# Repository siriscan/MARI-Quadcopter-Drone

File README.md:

# MARI-Quadcopter-Drone
A final senior project created by Seth Iris Canonigo, Christopher Ruiz-Guerra, Nahom Solomon, and Connor Prior

*(Omori is a good game btw)*

# 3D PCB

Read 'Report.pdf' for the full project writeup.

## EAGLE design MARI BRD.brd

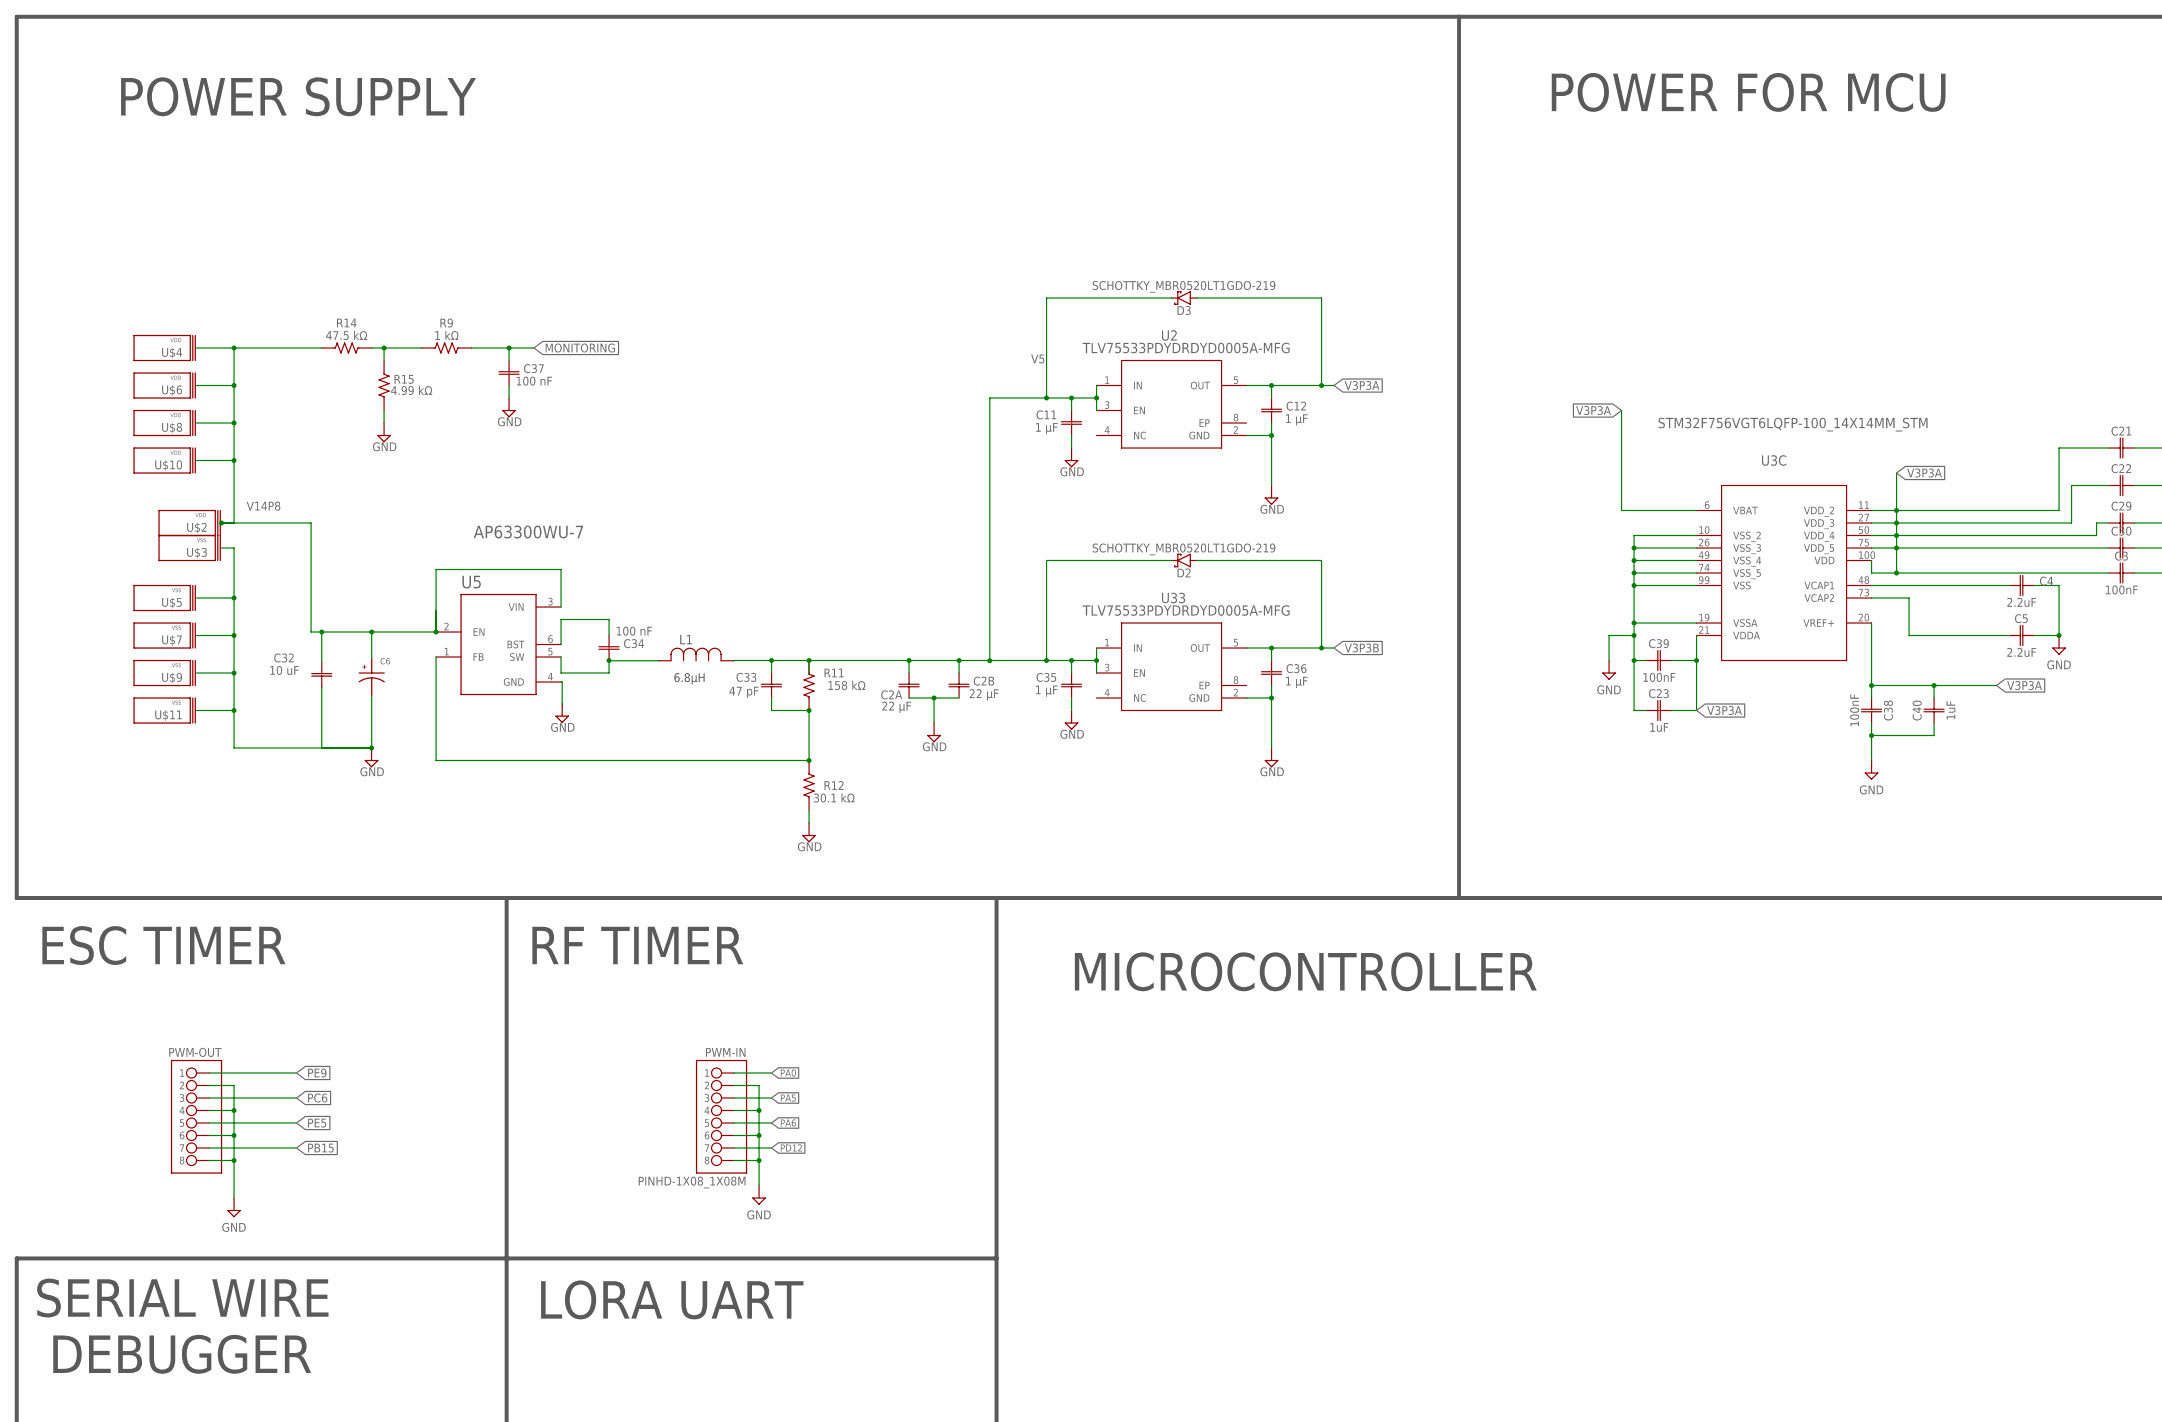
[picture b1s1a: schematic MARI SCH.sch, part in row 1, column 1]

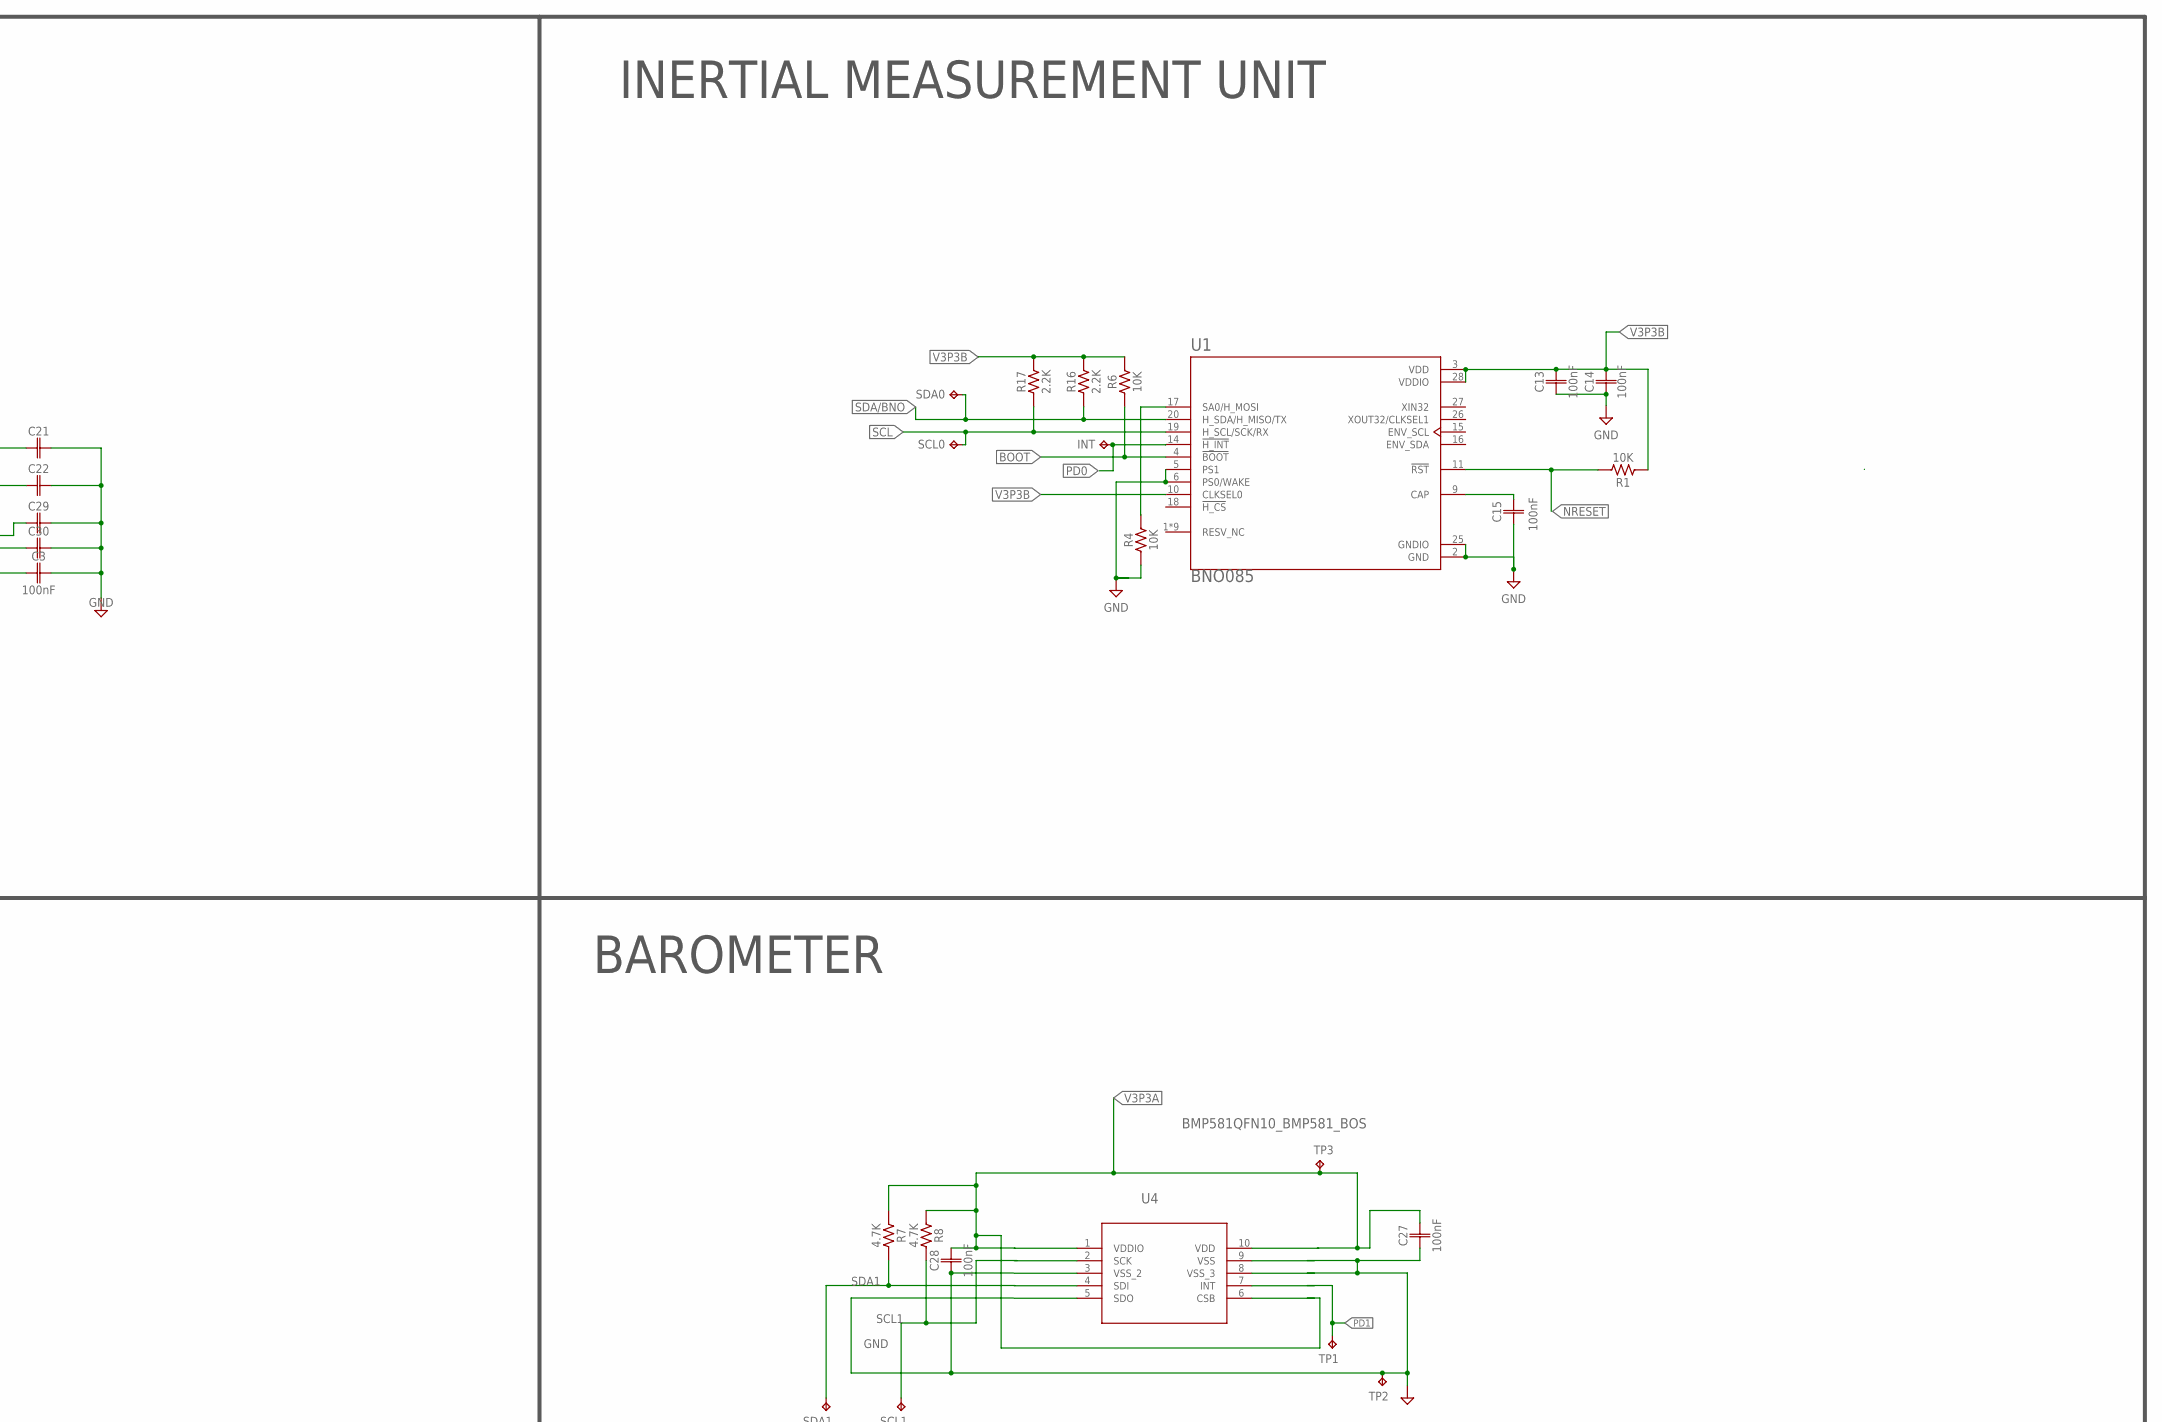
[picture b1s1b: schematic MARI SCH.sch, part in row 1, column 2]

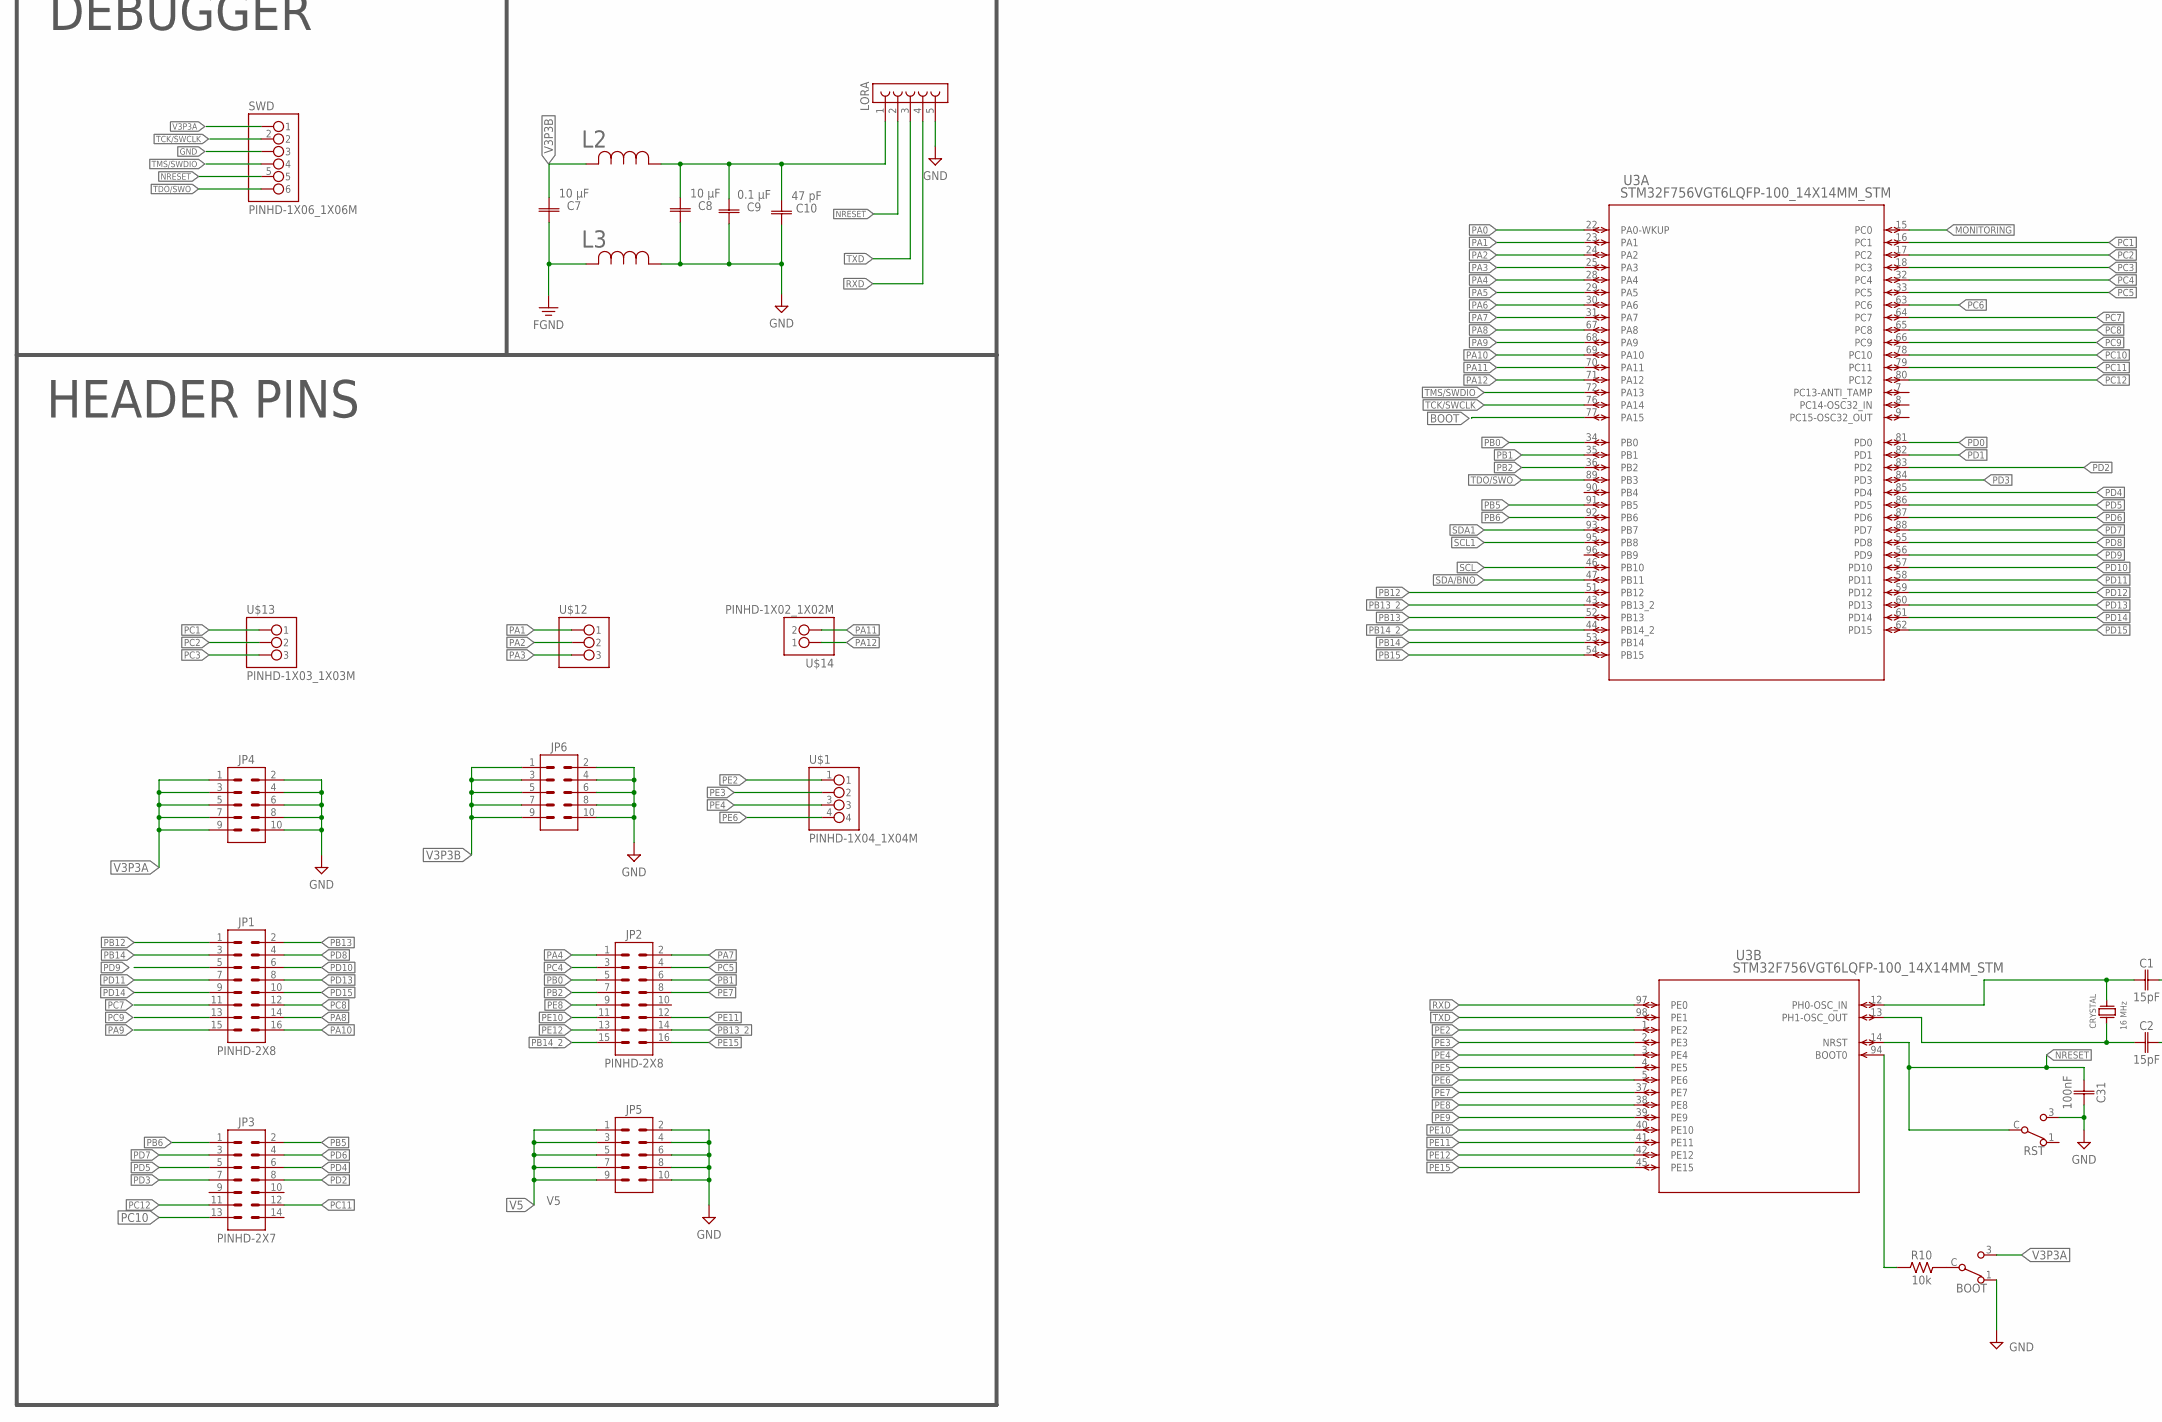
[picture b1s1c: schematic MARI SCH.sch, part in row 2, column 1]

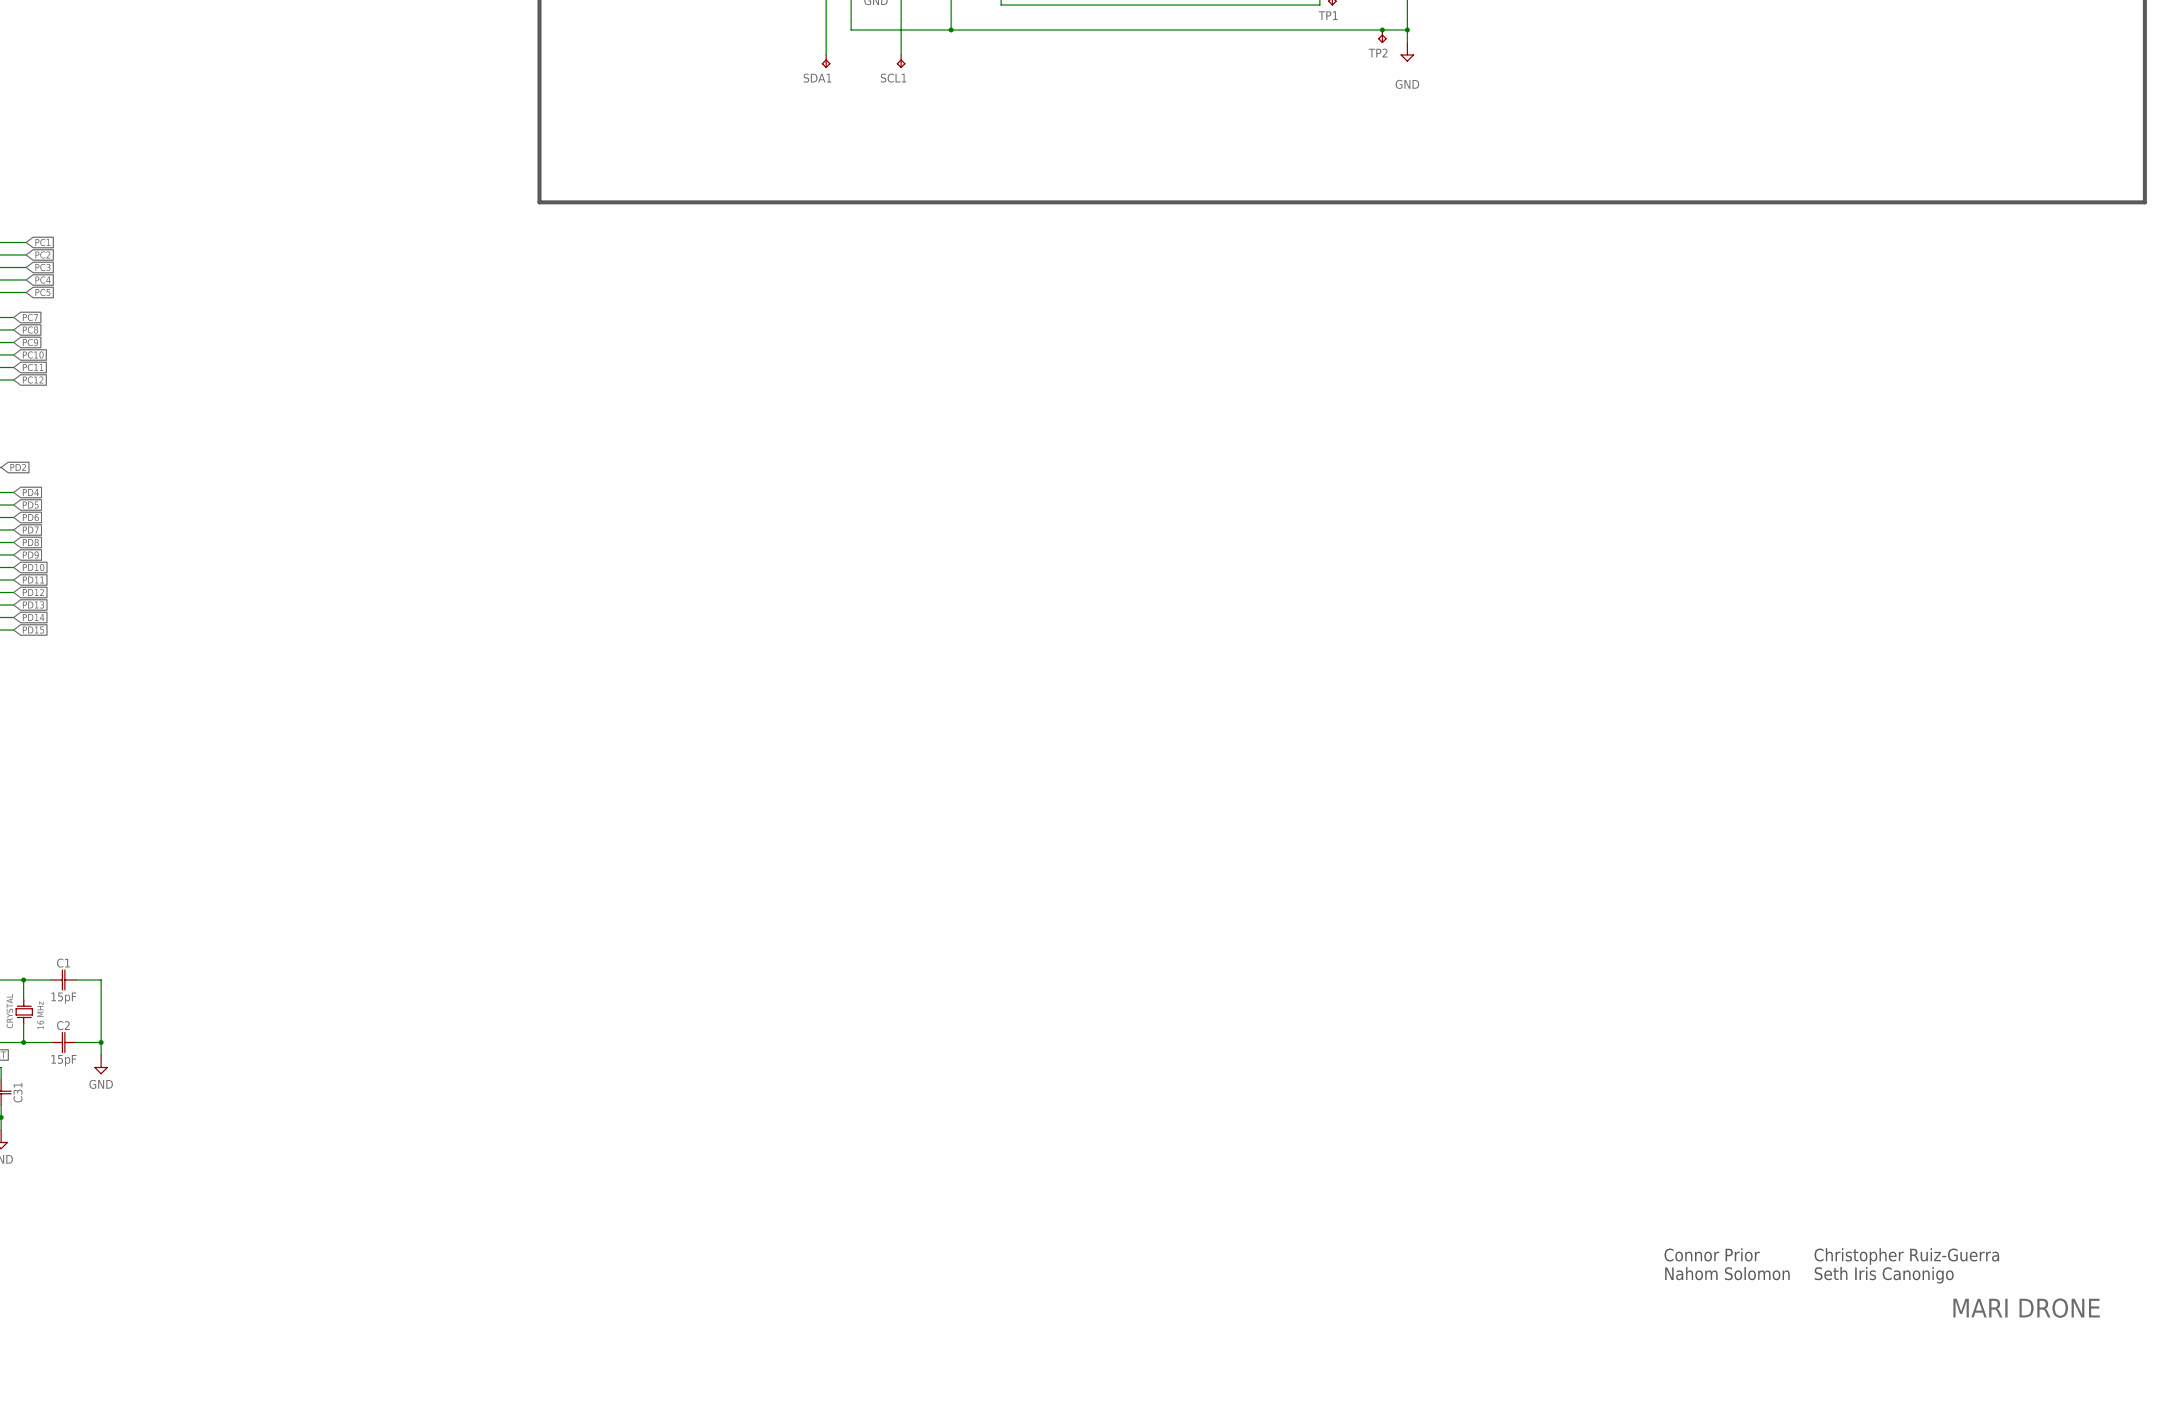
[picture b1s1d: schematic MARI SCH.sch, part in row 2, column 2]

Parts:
BOOT: SPDT_SWITCH_CL-SB-12B-01T; CL-SB-12B-01T
C1, C2: 15pF; CAPC1005X60
C2A, C2B: 22 µF; CAPC1005X60
C3, C13, C14, C15, C21, C22, C27, C28, C29, C30, C31, C38, C39: 100nF; CAPC1005X60
C4, C5: 2.2uF; CAPC1005X60
C6: B41866C5108M000; CAPPRD500W60D1250H2200
C7, C8: 10 µF; CAPC1005X60
C9: 0.1 µF; CAPC1005X60
C10, C33: 47 pF; CAPC1005X60
C11, C12, C35, C36: 1 µF; CAPC1005X60
C23, C40: 1uF; CAPC1005X60
C32: 10 uF; CAPC2012X110
C34, C37: 100 nF; CAPC1005X60
CRYSTAL: 16 MHz; STDCRG1-16M
D2, D3: SCHOTTKY_MBR0520LT1GDO-219; SODFL3718X115
INT: TPB1,27; B1,27
JP1, JP2: PINHD-2X8; 2X08
JP3: PINHD-2X7; 2X07
JP4, JP5, JP6: PINHD-2X5; 2X05
L1: 74437334068IND_WE-LHMI_5020_WRE; IND_WE-LHMI_5020_WRE
L2, L3: BLM15EG121SN1DIND_BLM15_0402_MUR-M; IND_BLM15_0402_MUR-M
LORA: FEMALE-HEADER-1X5; 1X05
PWM-IN: PINHD-1X08_1X08M; 1X08
PWM-OUT: PINHD-1X08_1X08M; 1X08
R1, R4, R6: 10K; RESC1005X40
R7, R8: 4.7K; RESC1005X40
R9: 1 kΩ; RESC1005X40
R10: 10k; RESC1005X40
R11: 158 kΩ; RESC1005X40
R12: 30.1 kΩ; RESC1005X40
R14: 47.5 kΩ; RESC1005X40
R15: 4.99 kΩ; RESC1005X40
R16, R17: 2.2K; RESC1005X40
RST: SPDT_SWITCH_CL-SB-12B-01T; CL-SB-12B-01T
SCL0, SCL1: TPB1,27; B1,27
SDA0, SDA1: TPB1,27; B1,27
SWD: PINHD-1X06_1X06M; 1X06
TP1, TP2, TP3: TPB1,27; B1,27
U1: BNO085; IC_BNO085
U2, U33: TLV75533PDYDRDYD0005A-MFG; DYD0005A-MFG
U3: STM32F756VGT6LQFP-100_14X14MM_STM; LQFP-100_14X14MM_STM
U4: BMP581QFN10_BMP581_BOS; QFN10_BMP581_BOS
U5: AP63300WU-7; SOT95P280X100-6N
U$1: PINHD-1X04_1X04M; 1X04
U$2, U$4, U$6, U$8, U$10: VDD; 4MM_PLUG
U$3, U$5, U$7, U$9, U$11: VSS; 4MM_PLUG
U$12, U$13: PINHD-1X03_1X03M; 1X03
U$14: PINHD-1X02_1X02M; 1X02

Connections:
BOOT: R6.1, U1.4 (!BOOT), U3.77 (PA15)
FGND: C7.1, L3.2
GND: BOOT.1 (NC), C1.2, C2.2, C2A.2, C2B.2, C3.2, C4.2, C5.2, C6.2, C8.1, C9.1, C10.1, C11.1, C12.1, C13.1, C14.1, C15.1, C21.2, C22.2, C23.1, C27.1, C28.1, C29.2, C30.2, C31.2, C32.1, C35.1, C36.1, C37.2, C38.2, C39.1, C40.1, JP4.2, JP4.4, JP4.6, JP4.8, JP4.10, JP5.2, JP5.4, JP5.6, JP5.8, JP5.10, JP6.2, JP6.4, JP6.6, JP6.8, JP6.10, L3.1, LORA.5, PWM-IN.2, PWM-IN.4, PWM-IN.6, PWM-IN.8, PWM-OUT.2, PWM-OUT.4, PWM-OUT.6, PWM-OUT.8, R4.1, R12.1, R15.1, RST.3 (NO), SWD.3, TP2.TP, U1.2 (GND), U1.5 (PS1), U1.6 (PS0/WAKE), U1.25 (GNDIO), U2.2 (GND), U3.10 (VSS_2), U3.19 (VSSA), U3.26 (VSS_3), U3.49 (VSS_4), U3.74 (VSS_5), U3.99 (VSS), U4.3 (VSS_2), U4.5 (SDO), U4.8 (VSS_3), U4.9 (VSS), U5.4 (GND), U33.2 (GND), U$3.P$1, U$5.P$1, U$7.P$1, U$9.P$1, U$11.P$1
MONITORING: C37.1, R9.2, U3.15 (PC0)
unnamed: C15.2, U1.9 (CAP)
unnamed: C8.2, C9.2, C10.2, L2.1, LORA.1
unnamed: C34.2, U5.6 (BST)
unnamed: R4.2, U1.17 (SA0/H_MOSI)
unnamed: C33.1, R11.1, R12.2, U5.1 (FB)
unnamed: C1.1, CRYSTAL.P$3, U3.12 (PH0-OSC_IN)
unnamed: C2.1, CRYSTAL.P$1, U3.13 (PH1-OSC_OUT)
unnamed: C4.1, U3.48 (VCAP1)
unnamed: C5.1, U3.73 (VCAP2)
unnamed: R10.1, U3.94 (BOOT0)
unnamed: BOOT.C (COM), R10.2
unnamed: R9.1, R14.1, R15.2
NRESET: C31.1, LORA.2, R1.2, RST.C (COM), SWD.5, U1.11 (!RST), U3.14 (NRST)
PA0: PWM-IN.1, U3.22 (PA0-WKUP)
PA1: U3.23 (PA1), U$12.1
PA2: U3.24 (PA2), U$12.2
PA3: U3.25 (PA3), U$12.3
PA4: JP2.1, U3.28 (PA4)
PA5: PWM-IN.3, U3.29 (PA5)
PA6: PWM-IN.5, U3.30 (PA6)
PA7: JP2.2, U3.31 (PA7)
PA8: JP1.14, U3.67 (PA8)
PA9: JP1.15, U3.68 (PA9)
PA10: JP1.16, U3.69 (PA10)
PA11: U3.70 (PA11), U$14.2
PA12: U3.71 (PA12), U$14.1
PB0: JP2.5, U3.34 (PB0)
PB1: JP2.6, U3.35 (PB1)
PB2: JP2.7, U3.36 (PB2)
PB5: JP3.2, U3.91 (PB5)
PB6: JP3.1, U3.92 (PB6)
PB12: JP1.1, U3.51 (PB12)
PB13: JP1.2, U3.52 (PB13)
PB13_2: JP2.14, U3.43 (PB13_2)
PB14: JP1.3, U3.53 (PB14)
PB14_2: JP2.15, U3.44 (PB14_2)
PB15: PWM-OUT.7, U3.54 (PB15)
PC1: U3.16 (PC1), U$13.1
PC2: U3.17 (PC2), U$13.2
PC3: U3.18 (PC3), U$13.3
PC4: JP2.3, U3.32 (PC4)
PC5: JP2.4, U3.33 (PC5)
PC6: PWM-OUT.3, U3.63 (PC6)
PC7: JP1.11, U3.64 (PC7)
PC8: JP1.12, U3.65 (PC8)
PC9: JP1.13, U3.66 (PC9)
PC10: JP3.13, U3.78 (PC10)
PC11: JP3.12, U3.79 (PC11)
PC12: JP3.11, U3.80 (PC12)
PD0: INT.TP, U1.14 (!H_INT), U3.81 (PD0)
PD1: TP1.TP, U3.82 (PD1), U4.7 (INT)
PD2: JP3.8, U3.83 (PD2)
PD3: JP3.7, U3.84 (PD3)
PD4: JP3.6, U3.85 (PD4)
PD5: JP3.5, U3.86 (PD5)
PD6: JP3.4, U3.87 (PD6)
PD7: JP3.3, U3.88 (PD7)
PD8: JP1.4, U3.55 (PD8)
PD9: JP1.5, U3.56 (PD9)
PD10: JP1.6, U3.57 (PD10)
PD11: JP1.7, U3.58 (PD11)
PD12: PWM-IN.7, U3.59 (PD12)
PD13: JP1.8, U3.60 (PD13)
PD14: JP1.9, U3.61 (PD14)
PD15: JP1.10, U3.62 (PD15)
PE2: U3.1 (PE2), U$1.1
PE3: U3.2 (PE3), U$1.2
PE4: U3.3 (PE4), U$1.3
PE5: PWM-OUT.5, U3.4 (PE5)
PE6: U3.5 (PE6), U$1.4
PE7: JP2.8, U3.37 (PE7)
PE8: JP2.9, U3.38 (PE8)
PE9: PWM-OUT.1, U3.39 (PE9)
PE10: JP2.11, U3.40 (PE10)
PE11: JP2.12, U3.41 (PE11)
PE12: JP2.13, U3.42 (PE12)
PE15: JP2.16, U3.45 (PE15)
RXD: LORA.4, U3.97 (PE0)
SCL: R17.1, SCL0.TP, U1.19 (H_SCL/SCK/RX), U3.46 (PB10)
SCL1: R8.2, SCL1.TP, U3.95 (PB8), U4.2 (SCK)
SDA1: R7.2, SDA1.TP, U3.93 (PB7), U4.4 (SDI)
SDA/BNO: R16.1, SDA0.TP, U1.20 (H_SDA/H_MISO/TX), U3.47 (PB11)
SW: C34.1, L1.2, U5.5 (SW)
TCK/SWCLK: SWD.2, U3.76 (PA14)
TDO/SWO: SWD.6, U3.89 (PB3)
TMS/SWDIO: SWD.4, U3.72 (PA13)
TXD: LORA.3, U3.98 (PE1)
V3P3A: BOOT.3 (NO), C3.1, C12.2, C21.1, C22.1, C23.2, C27.2, C28.2, C29.1, C30.1, C38.1, C39.2, C40.2, D3.2 (A), JP4.1, JP4.3, JP4.5, JP4.7, JP4.9, R7.1, R8.1, SWD.1, TP3.TP, U2.5 (OUT), U3.6 (VBAT), U3.11 (VDD_2), U3.20 (VREF+), U3.21 (VDDA), U3.27 (VDD_3), U3.50 (VDD_4), U3.75 (VDD_5), U3.100 (VDD), U4.1 (VDDIO), U4.6 (CSB), U4.10 (VDD)
V3P3B: C7.2, C13.2, C14.2, C36.2, D2.2 (A), JP6.1, JP6.3, JP6.5, JP6.7, JP6.9, L2.2, R1.1, R6.2, R16.2, R17.2, U1.3 (VDD), U1.10 (CLKSEL0), U1.28 (VDDIO), U33.5 (OUT)
V5: C2A.1, C2B.1, C11.2, C33.2, C35.2, D2.1 (C), D3.1 (C), JP5.1, JP5.3, JP5.5, JP5.7, JP5.9, L1.1, R11.2, U2.1 (IN), U2.3 (EN), U33.1 (IN), U33.3 (EN)
V14P8: C6.1, C32.2, R14.2, U5.2 (EN), U5.3 (VIN), U$2.P$1, U$4.P$1, U$6.P$1, U$8.P$1, U$10.P$1

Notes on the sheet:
MARI DRONE
Connor Prior Nahom Solomon
Christopher Ruiz-Guerra Seth Iris Canonigo
HEADER PINS
LORA UART
SERIAL WIRE DEBUGGER
ESC TIMER
RF TIMER
POWER SUPPLY
POWER FOR MCU
INERTIAL MEASUREMENT UNIT
BAROMETER
MICROCONTROLLER
6.8μH

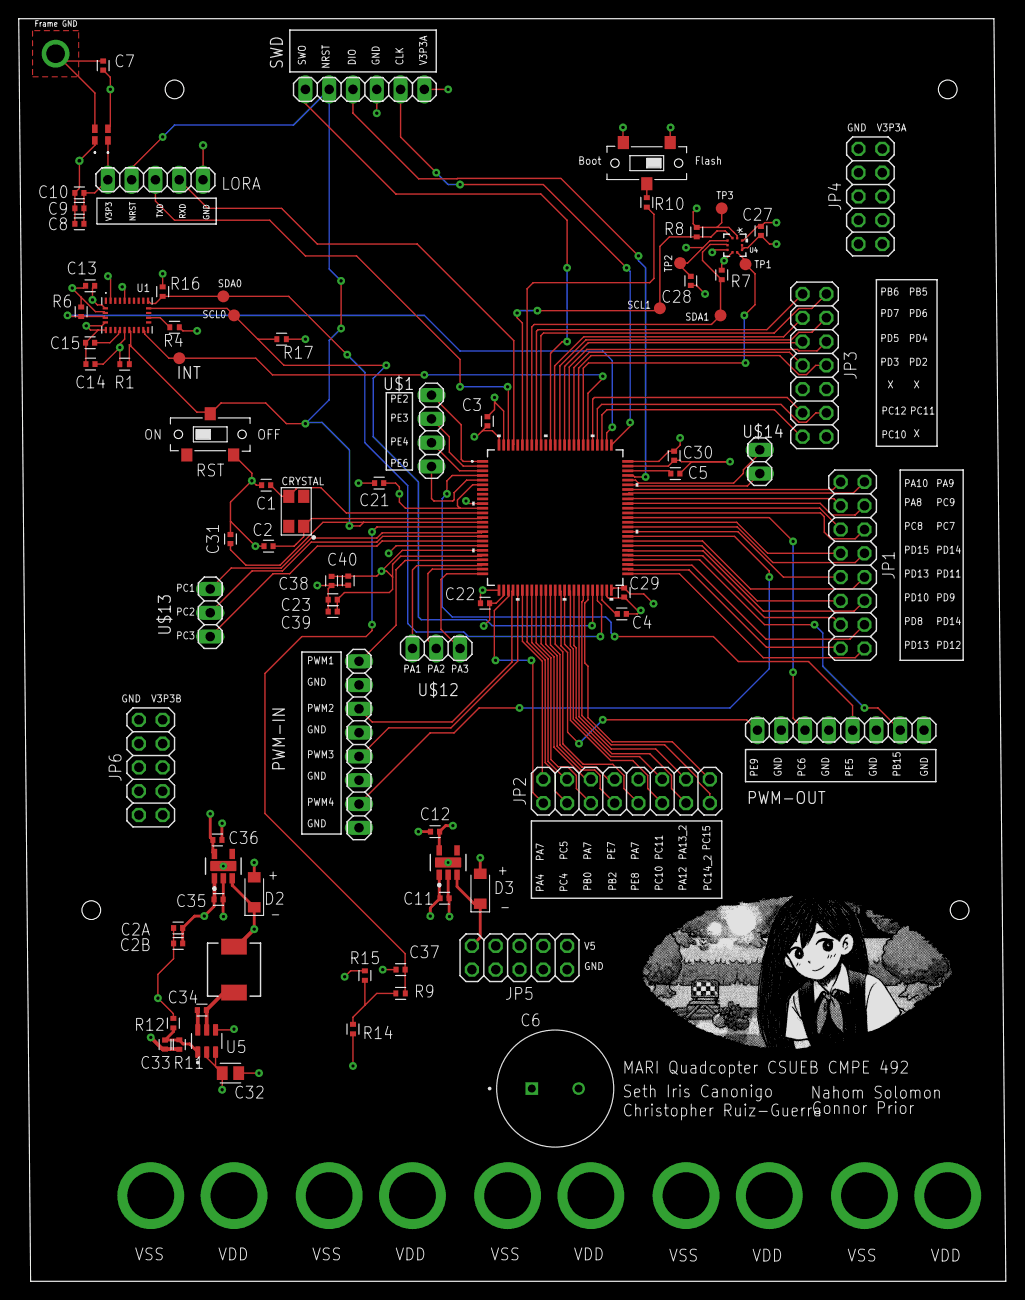
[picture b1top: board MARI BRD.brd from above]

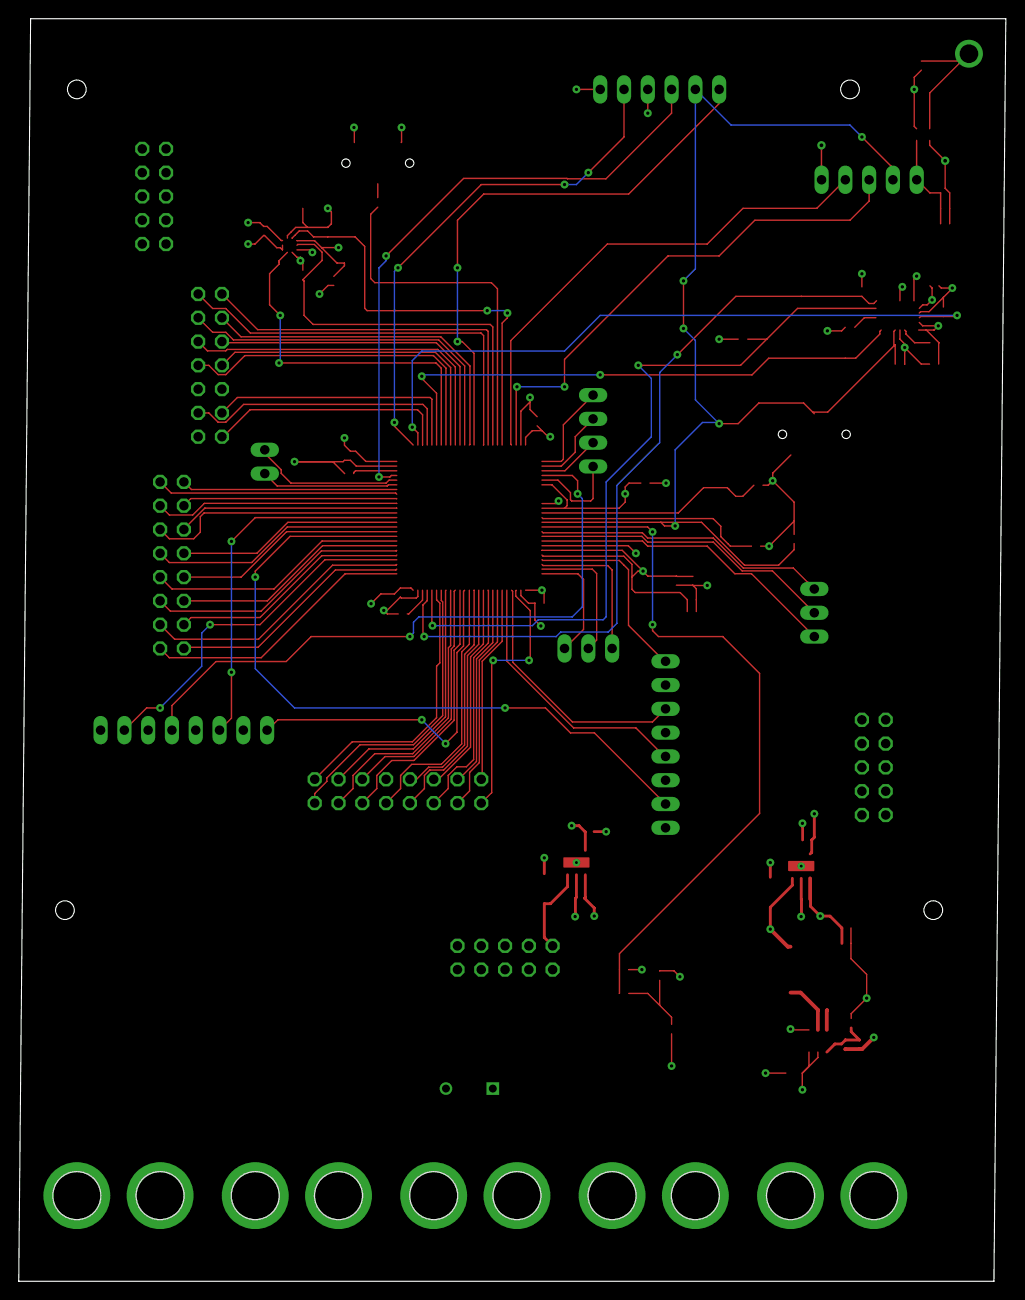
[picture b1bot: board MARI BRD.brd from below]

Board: 4 copper layers, 105.4 x 134.8 mm, 93 parts (10 on the bottom side), 95 nets.

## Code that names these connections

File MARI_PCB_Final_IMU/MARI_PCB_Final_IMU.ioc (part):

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Mcu.Name=STM32F756VGTx
Mcu.Package=LQFP100
Mcu.UserName=STM32F756VGTx
PA0/WKUP.Signal=S_TIM5_CH1
PA10.Signal=GPIO_Output
PA11.Signal=GPIO_Output
PA12.Signal=GPIO_Output
PA13.Mode=Serial_Wire
PA13.Signal=SYS_JTMS-SWDIO
PA14.Mode=Serial_Wire
PA14.Signal=SYS_JTCK-SWCLK
PA5.Signal=S_TIM2_CH1_ETR
PA6.Signal=S_TIM3_CH1
PB10.Mode=I2C
PB10.Signal=I2C2_SCL
PB11.Mode=I2C
PB11.Signal=I2C2_SDA
PB15.Signal=S_TIM12_CH2
PB7.Mode=I2C
PB7.Signal=I2C1_SDA
PB8.Mode=I2C
PB8.Signal=I2C1_SCL
PC0.Signal=ADCx_IN10
PC6.Signal=S_TIM8_CH1
PD0.GPIOParameters=GPIO_PuPd,GPIO_Label,GPIO_ModeDefaultEXTI
PD0.GPIO_Label=BNO_INTN
PD0.GPIO_ModeDefaultEXTI=GPIO_MODE_IT_FALLING
PD0.GPIO_PuPd=GPIO_PULLUP
PD0.Signal=GPXTI0
PD12.Signal=S_TIM4_CH1
PE0.Mode=Asynchronous
PE0.Signal=UART8_RX
PE1.Mode=Asynchronous
PE1.Signal=UART8_TX
PE5.Signal=S_TIM9_CH1
PE9.Signal=S_TIM1_CH1
PH0/OSC_IN.Mode=HSE-External-Oscillator
PH0/OSC_IN.Signal=RCC_OSC_IN
PH1/OSC_OUT.Mode=HSE-External-Oscillator
PH1/OSC_OUT.Signal=RCC_OSC_OUT
RCC.HSE_VALUE=16000000
RCC.SYSCLKFreq_VALUE=216000000
RCC.SYSCLKSource=RCC_SYSCLKSOURCE_PLLCLK
board=custom

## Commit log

2025-12-01 Add project title to README
2025-12-01 Swapped images
2025-12-01 Update README with project information and images
    Added project details, images, and a reference to the report.
2025-12-01 Added report
2025-12-12 Updated files
2026-03-13 Added CLI exe
2026-05-13 Updated to final

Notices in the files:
parts and their libraries:
COPYRIGHT: Copyright (C) 2025 Ultra Librarian. All rights reserved.
COPYRIGHT: Copyright (C) 2026 Ultra Librarian. All rights reserved.
